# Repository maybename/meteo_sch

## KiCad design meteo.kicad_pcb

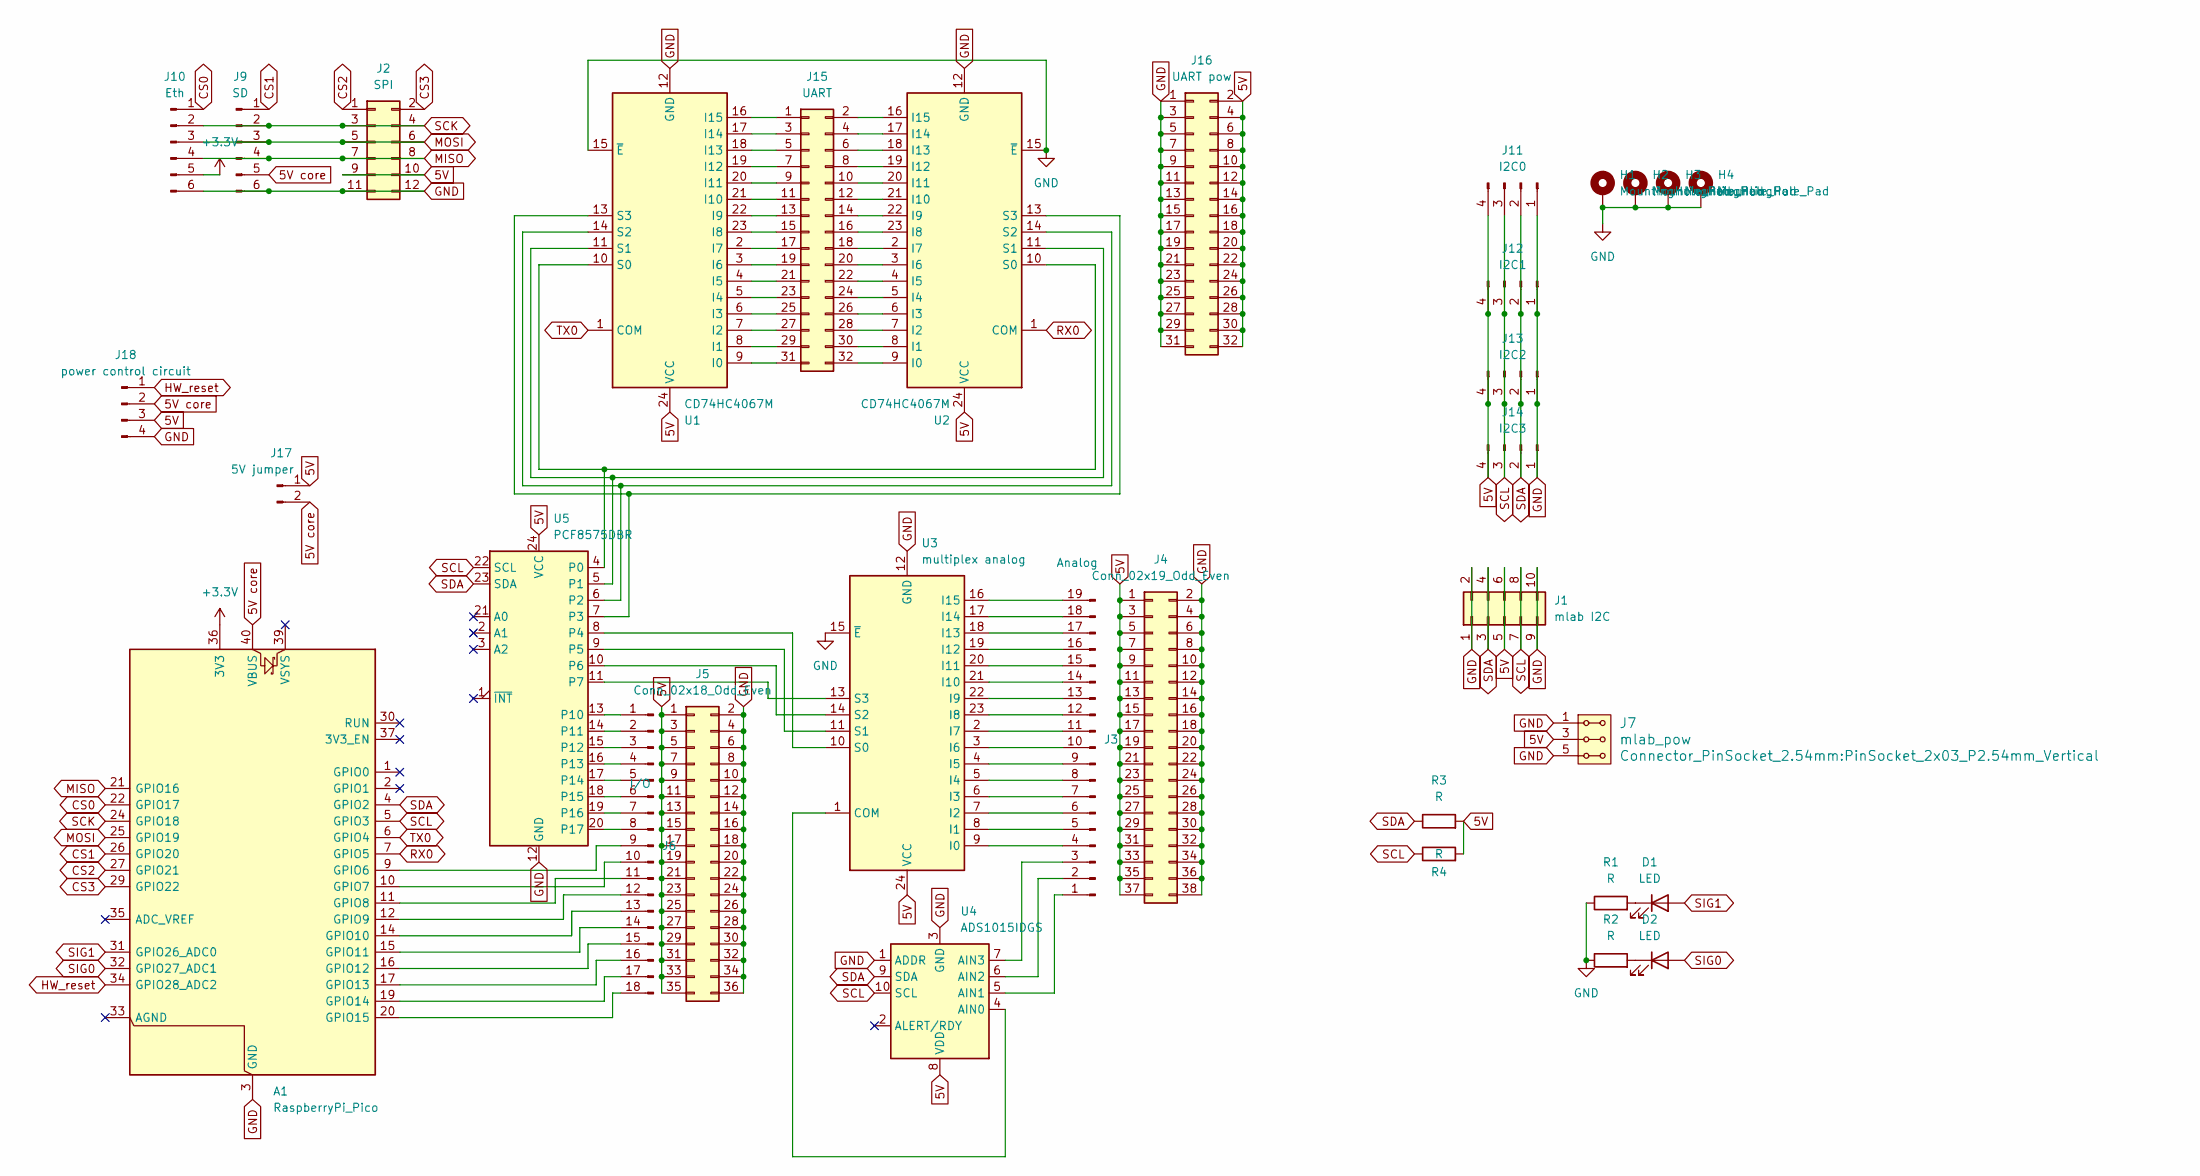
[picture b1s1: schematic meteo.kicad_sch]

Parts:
A1: RaspberryPi_Pico; RaspberryPi_Pico_Common_THT
D1, D2: LED; LED_D4.0mm
H1, H2, H3, H4: MountingHole_Pad; MountingHole_3.2mm_M3_DIN965_Pad
J1: mlab I2C; PinHeader_2x05_P2.54mm_Vertical
J2: SPI; PinHeader_2x06_P2.54mm_Vertical
J3: Analog; PinHeader_1x19_P2.54mm_Vertical
J4: Conn_02x19_Odd_Even; PinHeader_2x19_P2.54mm_Vertical
J5: Conn_02x18_Odd_Even; PinHeader_2x18_P2.54mm_Vertical
J6: I/O; PinHeader_1x18_P2.54mm_Vertical
J7: mlab_pow; PinSocket_2x03_P2.54mm_Vertical
J9: SD; Arduino microSD reader
J10: Eth; ENC28J60
J11: I2C0; JST_XH_B4B-XH-A_1x04_P2.50mm_Vertical
J12: I2C1; JST_XH_B4B-XH-A_1x04_P2.50mm_Vertical
J13: I2C2; JST_XH_B4B-XH-A_1x04_P2.50mm_Vertical
J14: I2C3; JST_XH_B4B-XH-A_1x04_P2.50mm_Vertical
J15: UART; PinHeader_2x16_P2.54mm_Vertical
J16: UART pow; PinHeader_2x16_P2.54mm_Vertical
J17: 5V jumper; PinHeader_1x02_P2.54mm_Vertical
J18: power control circuit; PinHeader_1x04_P2.54mm_Vertical
R1, R2, R3, R4: R; R_Axial_DIN0207_L6.3mm_D2.5mm_P15.24mm_Horizontal
U1, U2: CD74HC4067M; analogMultiplexer
U3: multiplex analog; analogMultiplexer
U4: ADS1015IDGS; ADS1115
U5: PCF8575DBR; IOexpander

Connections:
5V: J1.5, J1.6, J2.9, J2.10, J4.1, J4.3, J4.5, J4.7, J4.9, J4.11, J4.13, J4.15, J4.17, J4.19, J4.21, J4.23, J4.25, J4.27, J4.29, J4.31, J4.33, J4.35, J4.37, J5.1, J5.3, J5.5, J5.7, J5.9, J5.11, J5.13, J5.15, J5.17, J5.19, J5.21, J5.23, J5.25, J5.27, J5.29, J5.31, J5.33, J5.35, J7.3, J7.4, J11.4, J12.4, J13.4, J14.4, J16.2, J16.4, J16.6, J16.8, J16.10, J16.12, J16.14, J16.16, J16.18, J16.20, J16.22, J16.24, J16.26, J16.28, J16.30, J16.32, J17.1, J18.3, R3.2, R4.2, U1.24 (VCC), U2.24 (VCC), U3.24 (VCC), U4.8 (VDD), U5.24 (VCC)
5V core: A1.40 (VBUS), J9.5, J17.2, J18.2
+3.3V: A1.36 (3V3), J10.5
CS0: A1.22 (GPIO17), J10.1
CS1: A1.26 (GPIO20), J9.1
CS2: A1.27 (GPIO21), J2.1
CS3: A1.29 (GPIO22), J2.2
GND: A1.3 (GND), A1.8 (GND), A1.13 (GND), A1.18 (GND), A1.23 (GND), A1.28 (GND), A1.38 (GND), H1.1 (1_1), H2.1 (1_1), H3.1 (1_1), H4.1 (1_1), J1.1, J1.2, J1.9, J1.10, J2.11, J2.12, J4.2, J4.4, J4.6, J4.8, J4.10, J4.12, J4.14, J4.16, J4.18, J4.20, J4.22, J4.24, J4.26, J4.28, J4.30, J4.32, J4.34, J4.36, J4.38, J5.2, J5.4, J5.6, J5.8, J5.10, J5.12, J5.14, J5.16, J5.18, J5.20, J5.22, J5.24, J5.26, J5.28, J5.30, J5.32, J5.34, J5.36, J7.1, J7.2, J7.5, J7.6, J9.6, J10.6, J11.1, J12.1, J13.1, J14.1, J16.1, J16.3, J16.5, J16.7, J16.9, J16.11, J16.13, J16.15, J16.17, J16.19, J16.21, J16.23, J16.25, J16.27, J16.29, J16.31, J18.4, R1.1, R2.1, U1.12 (GND), U1.15 (~E), U2.12 (GND), U2.15 (~E), U3.12 (GND), U3.15 (~E), U4.1 (ADDR), U4.3 (GND), U5.12 (GND)
HW_reset: A1.34 (GPIO28_ADC2), J18.1
MISO: A1.21 (GPIO16), J2.7, J2.8, J9.4, J10.4
MOSI: A1.25 (GPIO19), J2.5, J2.6, J9.3, J10.3
unnamed: A1.9 (GPIO6), J6.9
unnamed: A1.10 (GPIO7), J6.10
unnamed: A1.11 (GPIO8), J6.11
unnamed: A1.12 (GPIO9), J6.12
unnamed: A1.14 (GPIO10), J6.13
unnamed: A1.15 (GPIO11), J6.14
unnamed: A1.16 (GPIO12), J6.15
unnamed: A1.17 (GPIO13), J6.16
unnamed: A1.19 (GPIO14), J6.17
unnamed: A1.20 (GPIO15), J6.18
unnamed: D1.1 (K), R1.2
unnamed: D2.1 (K), R2.2
unnamed: J3.1, U4.5 (AIN1)
unnamed: J3.2, U4.6 (AIN2)
unnamed: J3.3, U4.7 (AIN3)
unnamed: J3.4, U3.9 (I0)
unnamed: J3.5, U3.8 (I1)
unnamed: J3.6, U3.7 (I2)
unnamed: J3.7, U3.6 (I3)
unnamed: J3.8, U3.5 (I4)
unnamed: J3.9, U3.4 (I5)
unnamed: J3.10, U3.3 (I6)
unnamed: J3.11, U3.2 (I7)
unnamed: J3.12, U3.23 (I8)
unnamed: J3.13, U3.22 (I9)
unnamed: J3.14, U3.21 (I10)
unnamed: J3.15, U3.20 (I11)
unnamed: J3.16, U3.19 (I12)
unnamed: J3.17, U3.18 (I13)
unnamed: J3.18, U3.17 (I14)
unnamed: J3.19, U3.16 (I15)
unnamed: J6.1, U5.13 (P10)
unnamed: J6.2, U5.14 (P11)
unnamed: J6.3, U5.15 (P12)
unnamed: J6.4, U5.16 (P13)
unnamed: J6.5, U5.17 (P14)
unnamed: J6.6, U5.18 (P15)
unnamed: J6.7, U5.19 (P16)
unnamed: J6.8, U5.20 (P17)
unnamed: J15.1, U1.16 (I15)
unnamed: J15.2, U2.16 (I15)
unnamed: J15.3, U1.17 (I14)
unnamed: J15.4, U2.17 (I14)
unnamed: J15.5, U1.18 (I13)
unnamed: J15.6, U2.18 (I13)
unnamed: J15.7, U1.19 (I12)
unnamed: J15.8, U2.19 (I12)
unnamed: J15.9, U1.20 (I11)
unnamed: J15.10, U2.20 (I11)
unnamed: J15.11, U1.21 (I10)
unnamed: J15.12, U2.21 (I10)
unnamed: J15.13, U1.22 (I9)
unnamed: J15.14, U2.22 (I9)
unnamed: J15.15, U1.23 (I8)
unnamed: J15.16, U2.23 (I8)
unnamed: J15.17, U1.2 (I7)
unnamed: J15.18, U2.2 (I7)
unnamed: J15.19, U1.3 (I6)
unnamed: J15.20, U2.3 (I6)
unnamed: J15.21, U1.4 (I5)
unnamed: J15.22, U2.4 (I5)
unnamed: J15.23, U1.5 (I4)
unnamed: J15.24, U2.5 (I4)
unnamed: J15.25, U1.6 (I3)
unnamed: J15.26, U2.6 (I3)
unnamed: J15.27, U1.7 (I2)
unnamed: J15.28, U2.7 (I2)
unnamed: J15.29, U1.8 (I1)
unnamed: J15.30, U2.8 (I1)
unnamed: J15.31, U1.9 (I0)
unnamed: J15.32, U2.9 (I0)
unnamed: U1.10 (S0), U2.10 (S0), U5.4 (P0)
unnamed: U1.11 (S1), U2.11 (S1), U5.5 (P1)
unnamed: U1.14 (S2), U2.14 (S2), U5.6 (P2)
unnamed: U1.13 (S3), U2.13 (S3), U5.7 (P3)
unnamed: U3.1 (COM), U4.4 (AIN0)
unnamed: U3.10 (S0), U5.8 (P4)
unnamed: U3.11 (S1), U5.9 (P5)
unnamed: U3.14 (S2), U5.10 (P6)
unnamed: U3.13 (S3), U5.11 (P7)
RX0: A1.7 (GPIO5), U2.1 (COM)
SCK: A1.24 (GPIO18), J2.3, J2.4, J9.2, J10.2
SCL: A1.5 (GPIO3), J1.7, J1.8, J11.3, J12.3, J13.3, J14.3, R4.1, U4.10 (SCL), U5.22 (SCL)
SDA: A1.4 (GPIO2), J1.3, J1.4, J11.2, J12.2, J13.2, J14.2, R3.1, U4.9 (SDA), U5.23 (SDA)
SIG0: A1.32 (GPIO27_ADC1), D2.2 (A)
SIG1: A1.31 (GPIO26_ADC0), D1.2 (A)
TX0: A1.6 (GPIO4), U1.1 (COM)

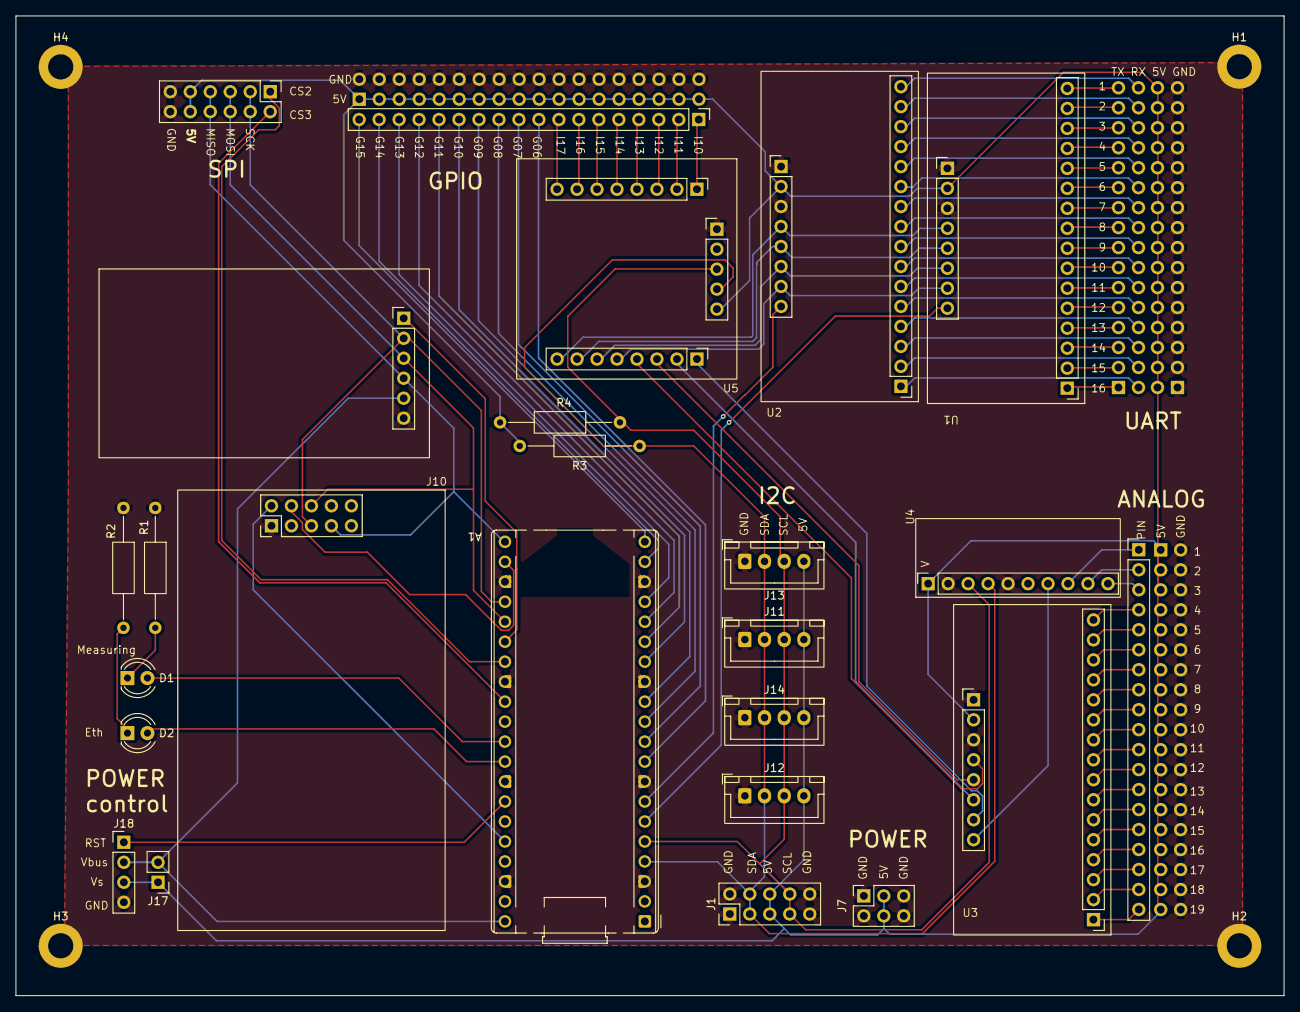
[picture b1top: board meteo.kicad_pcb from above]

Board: 2 copper layers, 161.2 x 124.5 mm, 33 parts (1 on the bottom side), 98 nets.
